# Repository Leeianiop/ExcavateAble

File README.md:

# ExcavatAble

## What is ExcavatAble? 
A robot designed for cave exploration, it manoeuvres left and right up and down using servos and motors, collects environmental data, and life feed of the environment. 

## Hardware 
3s 7200mah battery 
|----buck convert to 10.8v---pcb---drv8833: drive motor 
|----buck convert to 5v---pcb---esp32: to control movement of servo, sensors and servos 
|----buck convert to 6v---servo driver PCA9685: to power servo 

## PCB layout 
power terminal block input(5v)positive---capacitor25v 4200uf---esp32c3supermini 
power terminal block input(5v)negative 
| 
power terminal block output(5v)positive 
power terminal block output(5v)negative 

power terminal block input(10.8v)positive ----capacitor25v 4200uf---drv8833 motor driver---terminal block motor(left) 
power terminal block input(10.8v)negative                                             |---terminal block motor(right) 
| 
power terminal block output(10.8v)positive 
power terminal block output(10.8v)negative 

## CAD 
### Segment(1)---Main Segment(2)---Segment---Head Segment(3)  

### (1)Normal segment: pcb, two motors, 2suspension, two servos(vertical + horizontal movement)  
### (2)Main segment: 2pcb, four motors, two servos(vertical + horizontal movement),4suspensions   
### (3)Head segment: pcb, two motors, 2suspensions,rasberry pi 5 16gb   

### Battery and buck converters are in the main segment as labeled 
  
### To lock the suspension put in the spring first and screw along with a nut in each arrow  

### If you are a cool person and would like to install some sick RGB's install and link the wires link so

### Cable management is important !!, Trace them thorugh the holes ( Power cables and motor Cables )  

### Sensor attachment:  
ENS160+AHT21 and dht11 sensor, modular design swap out at any time, extra pin coming out of the PCB.   

## Software 

IT takes photos from a Raspberry Pi, processes them into a 3D mesh via a FastAPI backend, and renders them in a React + WebGL web viewer 
Quickstart: Run It Locally  
### 1. Start the Backend   
Head into the backend folder, set up your Python environment, and start the server. It will automatically fall back to local file storage and an in-memory job   store (so no Docker, Redis, or MinIO required).  

Bash
cd backend   
python -m venv .venv   
 Windows: .venv\Scripts\activate | Mac/Linux: source .venv/bin/activate   
pip install -r requirements.txt  
uvicorn app.main:app --host 0.0.0.0 --port 8000 --reload   
You’ll know it's working when you see the fallback warnings in the logs. Verify it at http://localhost:8000/api/v1/health.   
 
### 2. Start the Frontend  
Open a new terminal window for the frontend:  

Bash   
cd frontend  
npm install  
npm run dev  
Open http://localhost:5173 in your browser. You should see a green "Backend Connected" status.  

### 3. Run a Full Mock Scan (End-to-End)  
From the repo root directory (SnakeBot/), run the edge node simulation command:  
 
Bash  
python -m edge_node capture-and-upload --shots 20 --interval 0.1 --wait  
This generates synthetic photos, uploads them to your local backend, runs a mock 9-stage reconstruction pipeline, and outputs a job_id. Copy that job_id, paste it into the Job Lookup field on your frontend dashboard, and check out the rendered 3D mesh in the viewer.  

Using Real Hardware (Raspberry Pi 5 + Camera + Hailo-8L)  
If you want to use actual hardware:  

Find your computer's LAN IP (e.g., 192.168.1.50) so the Pi can reach your backend.  
 
Run the backend bound to all network interfaces:  

Bash  
uvicorn app.main:app --host 0.0.0.0 --port 8000  
Configure the Pi: SSH into your Raspberry Pi 5, navigate to edge_node/config/config.yaml, and update backend_url with your computer's LAN IP.  
 
Capture: Run your health checks and captures directly on the Pi:   

Bash   
python -m edge_node health-check   
python -m edge_node capture-and-upload --shots 20 --interval 1.5 --wait   
Default Ports & URLs   
Frontend UI: http://localhost:5173 (Demo map also available at /viewer/demo?format=demo)   

Backend API: http://localhost:8000   

API Docs: `   

Reflection:
One of the major challenges was how we kept burning the buck convertors and it's money from our own pocket going down the drain and so we weren't able to get everything done in a smooth steady condition, like every certain time there would be errors like loose motor wires, software issues and such.
-Ian Lee

Another challenge is that our pcb layout initial design due to the size constraints will definitely overheat, and we couldn't get good aluminium base pcb with good price, so we ended up making the fr4 four layers and used copper fill instead of line trace and hope for the best. Luckily it didn't overheat at all.
-Cyrus Ooi

All the problem combined had made us not able to deliver all we originally intended but we stil managed to work out a workable robot with the core functionality.

We have learned a lot from this project and are interested to expand and improve it in the future if we had the time, then our project would be impeccable.

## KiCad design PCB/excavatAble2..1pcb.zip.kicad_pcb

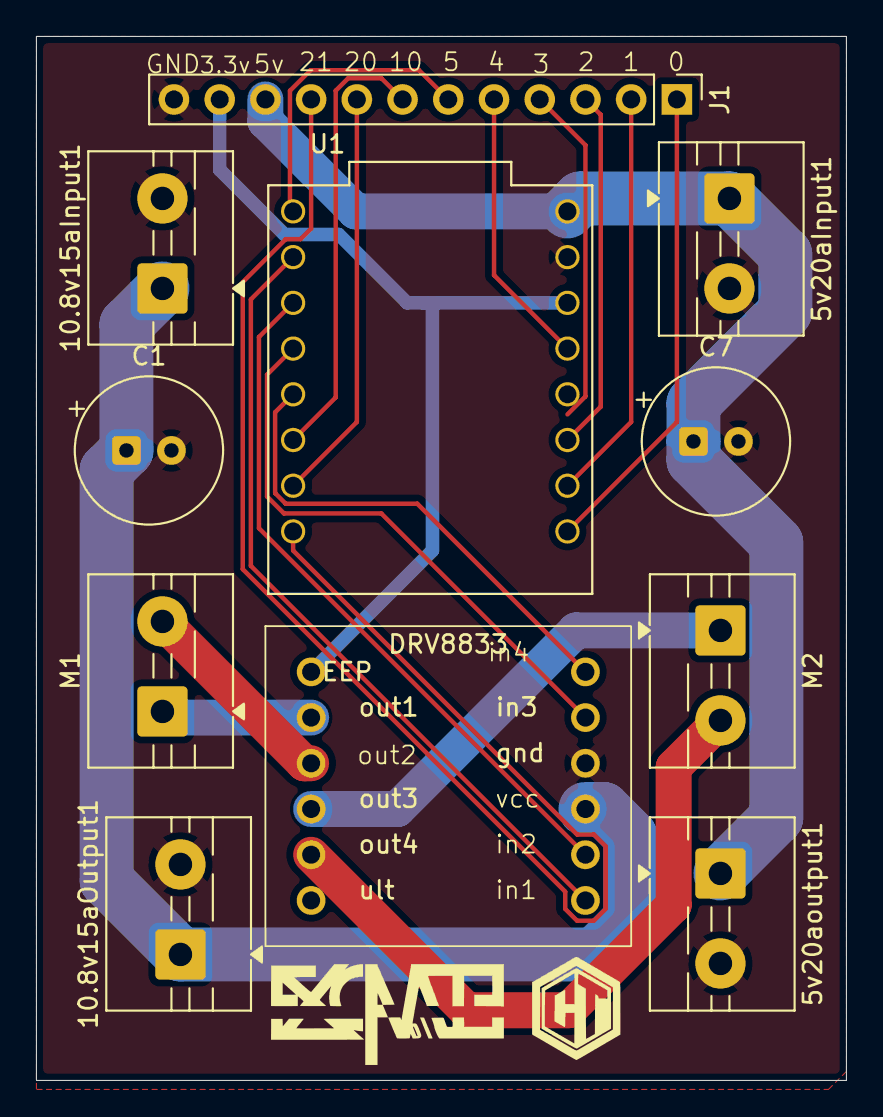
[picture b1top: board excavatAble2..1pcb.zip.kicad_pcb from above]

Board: 2 copper layers, 45.0 x 58.0 mm, 11 parts (0 on the bottom side), 21 nets.

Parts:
5v20aInput1, 5v20aoutput1, 10.8v15aInput1, 10.8v15aOutput1: Conn_01x02; TerminalBlock_MaiXu_MX126-5.0-02P_1x02_P5.00mm
C1, C7: C_Polarized; CP_Radial_Tantal_D8.0mm_P2.50mm
J1: Conn_01x12_Pin; PinHeader_1x12_P2.54mm_Vertical
M1, M2: Motor_DC; TerminalBlock_MaiXu_MX126-5.0-02P_1x02_P5.00mm
U1: ESP32-C3_SUPERMINI_TH; MODULE_ESP32-C3_SUPERMINI_TH
U3: drv8833module

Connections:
5v20aInput: 5v20aInput1.1, 5v20aoutput1.1, C7.1, J1.10, U1.5V
10.8v15AOutput: 10.8v15aInput1.1, 10.8v15aOutput1.1, C1.1, U3.10 (vcc)
GND: 5v20aInput1.2, 5v20aoutput1.2, 10.8v15aInput1.2, 10.8v15aOutput1.2, C1.2, C7.2, J1.12, U1.G (GND), U3.9 (gnd)
unnamed: J1.1, U1.0 (GPIO0)
unnamed: J1.2, U1.1 (GPIO1)
unnamed: J1.3, U1.2 (GPIO2)
unnamed: J1.4, U1.3 (GPIO3)
unnamed: J1.5, U1.4 (GPIO4)
unnamed: J1.6, U1.5 (GPIO5)
unnamed: J1.7, U1.10 (GPIO10)
unnamed: J1.8, U1.20 (GPIO20)
unnamed: J1.9, U1.21 (GPIO21)
unnamed: J1.11, U1.3.3 (3V3), U3.1 (eep)
unnamed: M1.1 (+), U3.2 (out1)
unnamed: M1.2 (-), U3.3 (out2)
unnamed: M2.1 (+), U3.4 (out3)
unnamed: M2.2 (-), U3.5 (out4)
unnamed: U1.6 (GPIO6), U3.12 (in1)
unnamed: U1.7 (GPIO7), U3.11 (in2)
unnamed: U1.8 (GPIO8), U3.8 (in3)
unnamed: U1.9 (GPIO9), U3.7 (in4)
